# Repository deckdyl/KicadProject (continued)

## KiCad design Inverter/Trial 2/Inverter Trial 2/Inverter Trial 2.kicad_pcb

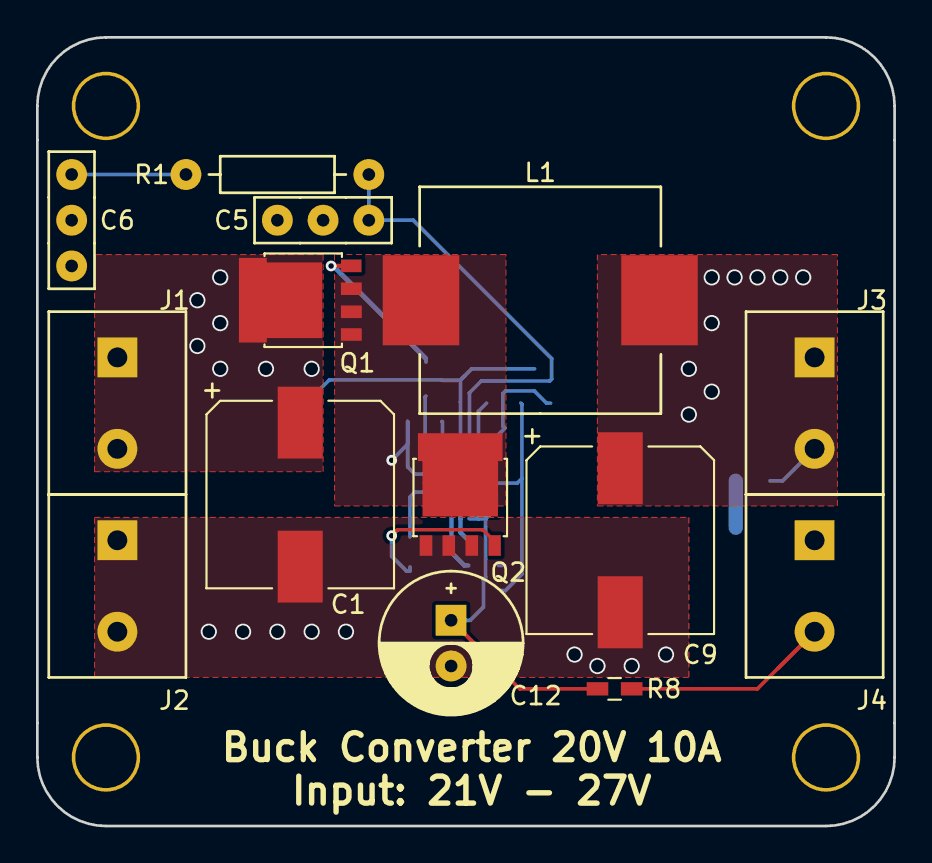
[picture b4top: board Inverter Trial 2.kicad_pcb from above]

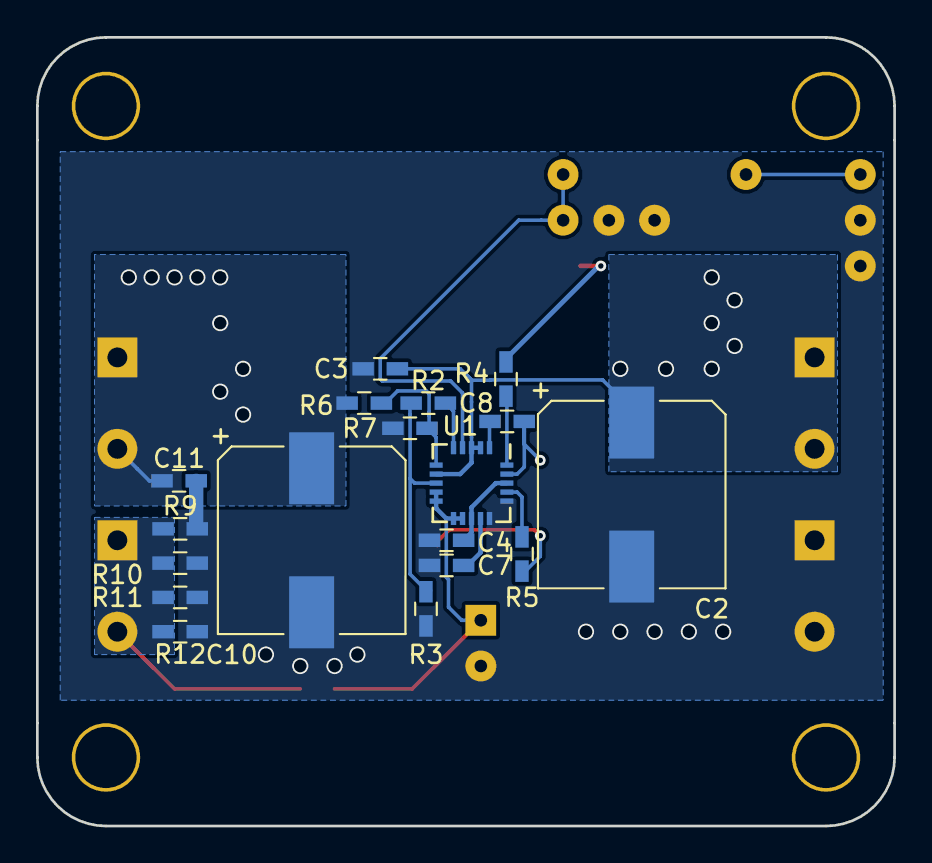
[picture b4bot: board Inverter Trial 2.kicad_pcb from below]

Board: 2 copper layers, 47.6 x 43.8 mm, 32 parts (18 on the bottom side), 18 nets.

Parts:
C1, C2, C9, C10: 330uF; CP_Elec_10x10.5
C3, C7, C8, C11: 100nF; C_0603_HandSoldering
C4: 1uF; C_0603_HandSoldering
C5: 220pF; Cap_UnPol_P3
C6: 2.2nF; Cap_UnPol_P3
C12: 10uF; Cap_Pol_Radial_D8_P2
J1: Battery+; Terminal_Block-5mm
J2: Battery-; Terminal_Block-5mm
J3: Vout+; Terminal_Block-5mm
J4: Vout-; Terminal_Block-5mm
L1: 2.2uH; Inductor_SMD_13X13
Q1, Q2: PSMN2R6-40YS; SOT-669_LFPAK
R1: 300kΩ; Resistor-0.25W
R2: 42.2kΩ; C_0603_HandSoldering
R3: 6.04kΩ; C_0603_HandSoldering
R4, R5, R8: 100Ω; C_0603_HandSoldering
R6: 18.7kΩ; C_0603_HandSoldering
R7: 1.2kΩ; C_0603_HandSoldering
R9, R10, R11, R12: 20mΩ; C_0603_HandSoldering
U1: TD8655; QFN-20-1EP_4x4mm_Pitch0.5mm

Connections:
/Vfb: R6.1, R7.2, U1.6
GND: C1.2, C2.2, C3.2, C4.2, C5.2, C6.2, C7.2, C9.2, C10.2, C11.2, C12.2, J2.1, J2.2, Q2.1, Q2.2, Q2.3, R3.1, R7.1, R9.1, R10.1, R11.1, R12.1, U1.15, U1.16
unnamed: C1.1, C2.1, C3.1, J1.1, J1.2, Q1.5, U1.2, U1.3, U1.7
unnamed: C4.1, U1.13, U1.18
unnamed: C5.1, R1.2, U1.4
unnamed: C6.1, R1.1
unnamed: C7.1, U1.14
unnamed: C8.1, U1.1
unnamed: C8.2, L1.1, Q1.1, Q1.2, Q1.3, Q2.5, U1.19
unnamed: C9.1, C10.1, C11.1, J3.1, J3.2, L1.2, R6.2
unnamed: C12.1, R8.2, U1.9, U1.10, U1.11, U1.12
unnamed: J4.1, J4.2, R8.1, R9.2, R10.2, R11.2, R12.2
unnamed: Q1.4, R4.1
unnamed: Q2.4, R5.1
unnamed: R2.1, R3.2, U1.8
unnamed: R2.2, U1.5
unnamed: R4.2, U1.20
unnamed: R5.2, U1.17

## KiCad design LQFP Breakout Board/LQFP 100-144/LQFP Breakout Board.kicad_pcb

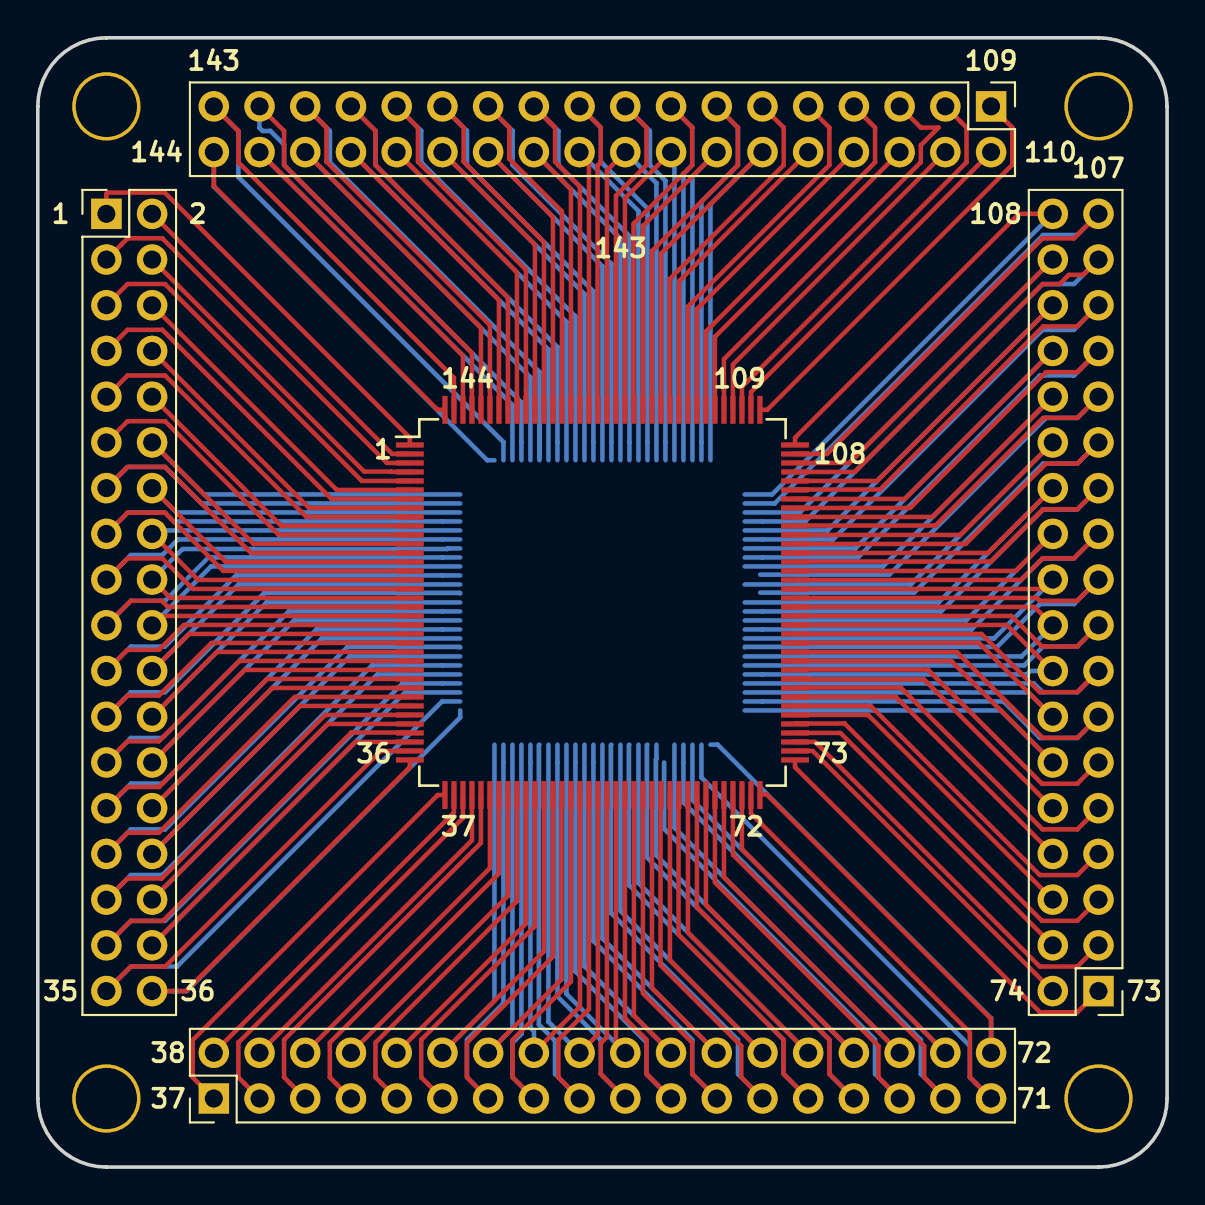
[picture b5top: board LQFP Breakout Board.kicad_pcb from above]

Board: 2 copper layers, 62.7 x 62.7 mm, 6 parts (1 on the bottom side), 144 nets.

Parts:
J1, J2, J3, J4: Conn_02x18_Odd_Even; Pin_Header_Straight_2x18_Pitch2.54mm
U1: STM32F446VET6; LQFP-100_14x14mm_Pitch0.5mm
U2: STM32F767ZITx; LQFP-144_20x20mm_Pitch0.5mm

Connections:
P01: J1.1, U2.1
P02: J1.2, U2.2
P03: J1.3, U2.3
P04: J1.4, U2.4
P05: J1.5, U2.5
P06: J1.6, U2.6
P07: J1.7, U2.7
P08: J1.8, U2.8
P09: J1.9, U2.9
P10: J1.10, U2.10
P11: J1.11, U2.11
P12: J1.12, U1.100, U2.12
P13: J1.13, U1.99, U2.13
P14: J1.14, U1.98, U2.14
P15: J1.15, U1.97, U2.15
P16: J1.16, U1.96, U2.16
P17: J1.17, U1.95, U2.17
P18: J1.18, U1.94, U2.18
P19: J1.19, U1.93, U2.19
P20: J1.20, U1.92, U2.20
P21: J1.21, U1.91, U2.21
P22: J1.22, U1.90, U2.22
P23: J1.23, U1.89, U2.23
P24: J1.24, U1.88, U2.24
P25: J1.25, U1.87, U2.25
P26: J1.26, U1.86, U2.26
P27: J1.27, U1.85, U2.27
P28: J1.28, U1.84, U2.28
P29: J1.29, U1.83, U2.29
P30: J1.30, U1.82, U2.30
P31: J1.31, U1.81, U2.31
P32: J1.32, U1.80, U2.32
P33: J1.33, U1.79, U2.33
P34: J1.34, U1.78, U2.34
P35: J1.35, U1.77, U2.35
P36: J1.36, U1.76, U2.36
P37: J2.1, U2.37
P38: J2.2, U2.38
P39: J2.3, U2.39
P40: J2.4, U2.40
P41: J2.5, U2.41
P42: J2.6, U2.42
P43: J2.7, U2.43
P44: J2.8, U2.44
P45: J2.9, U2.45
P46: J2.10, U2.46
P47: J2.11, U2.47
P48: J2.12, U1.75, U2.48
P49: J2.13, U1.74, U2.49
P50: J2.14, U1.73, U2.50
P51: J2.15, U1.72, U2.51
P52: J2.16, U1.71, U2.52
P53: J2.17, U1.70, U2.53
P54: J2.18, U1.69, U2.54
P55: J2.19, U1.68, U2.55
P56: J2.20, U1.67, U2.56
P57: J2.21, U1.66, U2.57
P58: J2.22, U1.65, U2.58
P59: J2.23, U1.64, U2.59
P60: J2.24, U1.63, U2.60
P61: J2.25, U1.62, U2.61
P62: J2.26, U1.61, U2.62
P63: J2.27, U1.60, U2.63
P64: J2.28, U1.59, U2.64
P65: J2.29, U1.58, U2.65
P66: J2.30, U1.57, U2.66
P67: J2.31, U1.56, U2.67
P68: J2.32, U1.55, U2.68
P69: J2.33, U1.54, U2.69
P70: J2.34, U1.53, U2.70
P71: J2.35, U1.52, U2.71
P72: J2.36, U1.51, U2.72
P73: J3.1, U2.73
P74: J3.2, U2.74
P75: J3.3, U2.75
P76: J3.4, U2.76
P77: J3.5, U2.77
P78: J3.6, U2.78
P79: J3.7, U2.79
P80: J3.8, U2.80
P81: J3.9, U2.81
P82: J3.10, U2.82
P83: J3.11, U2.83
P84: J3.12, U1.50, U2.84
P85: J3.13, U1.49, U2.85
P86: J3.14, U1.48, U2.86
P87: J3.15, U1.47, U2.87
P88: J3.16, U1.46, U2.88
P89: J3.17, U1.45, U2.89
P90: J3.18, U1.44, U2.90
P91: J3.19, U1.43, U2.91
P92: J3.20, U1.42, U2.92
P93: J3.21, U1.41, U2.93
P94: J3.22, U1.40, U2.94
P95: J3.23, U1.39, U2.95
P96: J3.24, U1.38, U2.96
P97: J3.25, U1.37, U2.97
P98: J3.26, U1.36, U2.98
P99: J3.27, U1.35, U2.99
P100: J3.28, U1.34, U2.100
P101: J3.29, U1.33, U2.101
P102: J3.30, U1.32, U2.102
P103: J3.31, U1.31, U2.103
P104: J3.32, U1.30, U2.104
P105: J3.33, U1.29, U2.105
P106: J3.34, U1.28, U2.106
P107: J3.35, U1.27, U2.107
P108: J3.36, U1.26, U2.108
P109: J4.1, U2.109
P110: J4.2, U2.110
P111: J4.3, U2.111
P112: J4.4, U2.112
P113: J4.5, U2.113
P114: J4.6, U2.114
P115: J4.7, U2.115
P116: J4.8, U2.116
P117: J4.9, U2.117
P118: J4.10, U2.118
P119: J4.11, U2.119
P120: J4.12, U1.25, U2.120
P121: J4.13, U1.24, U2.121
P122: J4.14, U1.23, U2.122
P123: J4.15, U1.22, U2.123
P124: J4.16, U1.21, U2.124
P125: J4.17, U1.20, U2.125
P126: J4.18, U1.19, U2.126
P127: J4.19, U1.18, U2.127
P128: J4.20, U1.17, U2.128
P129: J4.21, U1.16, U2.129
P130: J4.22, U1.15, U2.130
P131: J4.23, U1.14, U2.131
P132: J4.24, U1.13, U2.132
P133: J4.25, U1.12, U2.133
P134: J4.26, U1.11, U2.134
P135: J4.27, U1.10, U2.135
P136: J4.28, U1.9, U2.136
P137: J4.29, U1.8, U2.137
P138: J4.30, U1.7, U2.138
P139: J4.31, U1.6, U2.139
P140: J4.32, U1.5, U2.140
P141: J4.33, U1.4, U2.141
P142: J4.34, U1.3, U2.142
P143: J4.35, U1.2, U2.143
P144: J4.36, U1.1, U2.144

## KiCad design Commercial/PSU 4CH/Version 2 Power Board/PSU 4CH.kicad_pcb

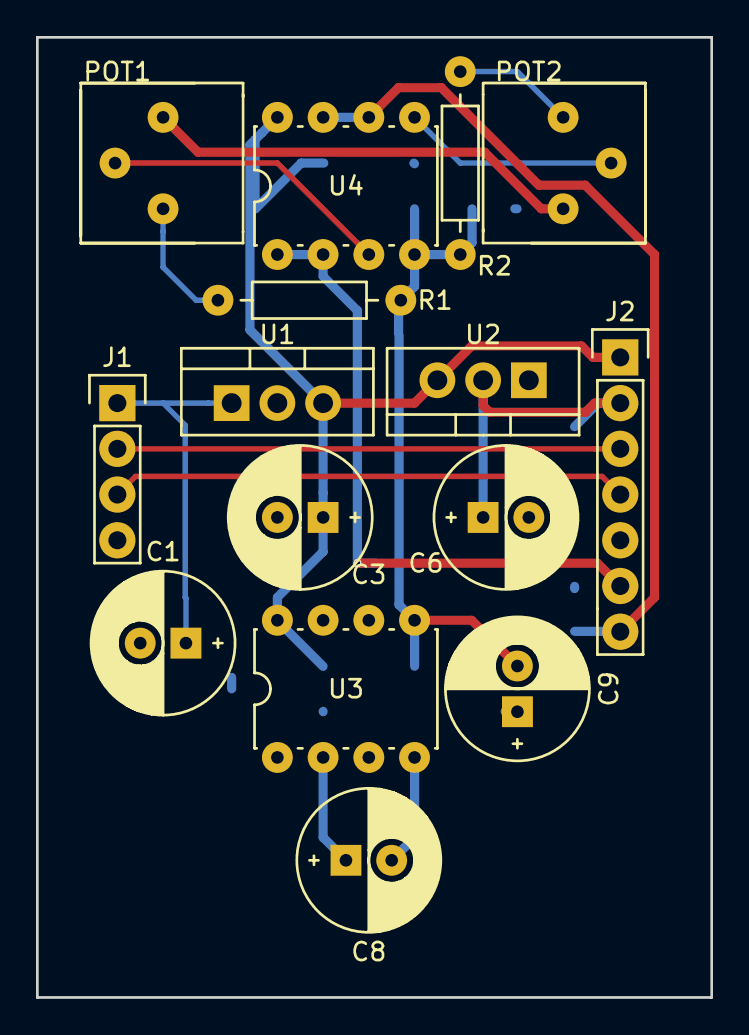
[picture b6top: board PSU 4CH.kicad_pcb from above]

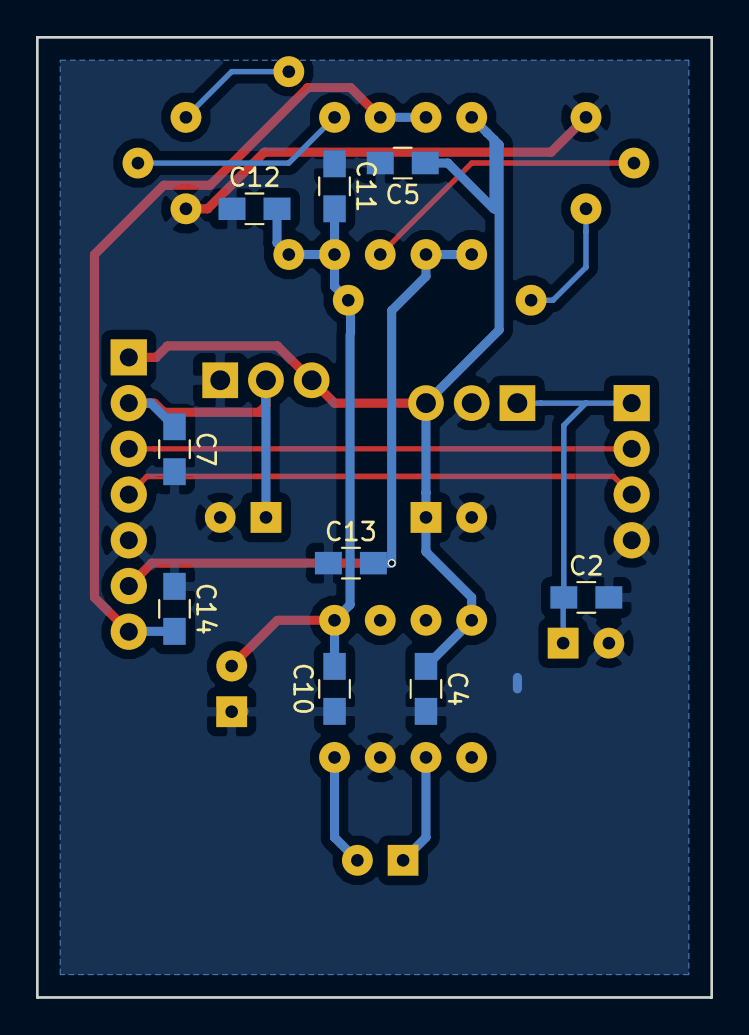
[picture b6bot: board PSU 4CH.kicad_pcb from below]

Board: 2 copper layers, 37.5 x 53.3 mm, 24 parts (9 on the bottom side), 15 nets.

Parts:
C1, C3, C6, C8, C9: 10uF; Cap_Pol_Radial_D8_P2
C2, C4, C5, C7, C10, C11, C12, C13, C14: 100nF; C_0805_HandSoldering
J1: I/O; Pin_Header_Straight_1x04
J2: PSU 4CH I/O; Pin_Header_Straight_1x07
POT1: 1kΩ; Potentiometer_Bourns_3386
POT2: 10K; Potentiometer_Bourns_3386
R1: 7K5; Resistor-0.25W
R2: 6K8; Resistor-0.25W
U1: L7805; TO-220_Neutral123_Vertical
U2: LD1117-3V3; TO-220_Neutral123_Vertical
U3: TC7662; IC_PDIP_8pin
U4: LM358; IC_PDIP_8pin

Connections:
+3V3: C6.1, C7.1, J2.2, U2.2
+5V: C3.1, C4.1, C5.1, J2.1, U1.3, U2.3, U3.8, U4.8
-0V5: C13.2, J2.6, U4.1, U4.2
-2V8: C14.2, J2.7, U4.6, U4.7
-5V: C9.2, C10.2, C11.2, C12.2, R1.1, R2.1, U3.5, U4.4
GND: C1.2, C2.2, C3.2, C4.2, C5.2, C6.2, C7.2, C9.1, C10.1, C11.1, C12.1, C13.1, C14.1, J1.4, J2.5, POT1.3, POT2.3, U1.2, U2.1, U3.3
unnamed: C8.1, U3.2
unnamed: C8.2, U3.4
unnamed: J1.2, J2.3
unnamed: J1.3, J2.4
unnamed: POT1.1, R1.2
unnamed: POT1.2, U4.3
unnamed: POT2.1, R2.2
unnamed: POT2.2, U4.5
Vin: C1.1, C2.1, J1.1, U1.1

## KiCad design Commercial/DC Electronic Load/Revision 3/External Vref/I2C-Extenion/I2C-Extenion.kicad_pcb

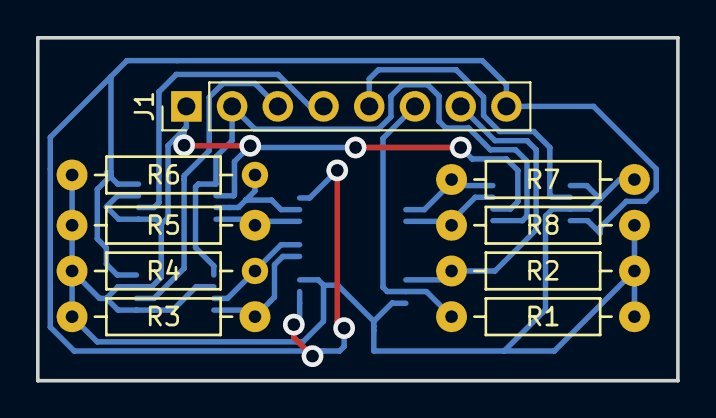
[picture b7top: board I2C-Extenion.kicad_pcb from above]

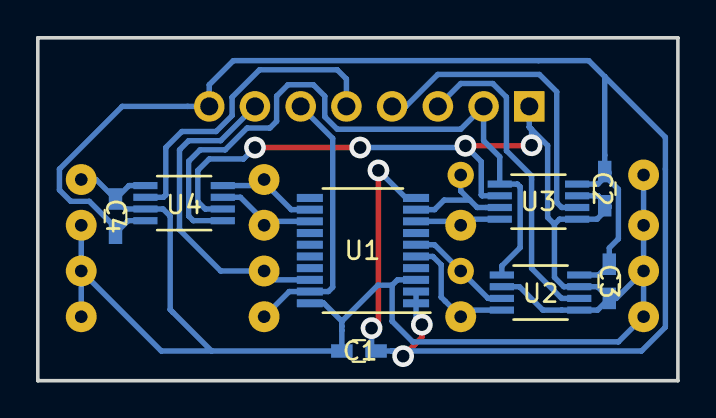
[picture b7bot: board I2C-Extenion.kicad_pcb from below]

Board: 2 copper layers, 35.6 x 19.1 mm, 17 parts (8 on the bottom side), 14 nets.

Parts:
C1, C2, C3, C4: 100nF; C_0603_HandSoldering
J1: Connector; Pin_Header_Straight_1x08_Pitch2.54mm
R1, R2, R3, R4, R5, R6, R7, R8: 10kΩ; Resistor-0.25W
U1: PCA9545; TSSOP-20_4.4x6.5mm_Pitch0.65mm
U2, U3, U4: MAX5215; uMAX

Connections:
1V-REF: J1.3, U2.6
2V5-REF: J1.4, U3.6
4V-REF: J1.5, U4.6
5V-REF: J1.2, U2.1, U3.1, U4.1
+3V3: C1.1, C2.1, C3.1, C4.1, J1.1, R1.1, R2.1, R3.1, R4.1, R5.1, R6.1, R7.1, R8.1, U1.3, U1.20, U2.2, U2.5, U2.7, U3.2, U3.5, U3.7, U4.2, U4.5, U4.7
GND: C1.2, C2.2, C3.2, C4.2, J1.8, U1.1, U1.2, U1.10, U2.8, U3.8, U4.8
I2C_SCL: J1.7, R2.2, U1.18
I2C_SDA: J1.6, R1.2, U1.19
unnamed: R3.2, U1.5, U2.4
unnamed: R4.2, U1.6, U2.3
unnamed: R5.2, U1.8, U3.4
unnamed: R6.2, U1.9, U3.3
unnamed: R7.2, U1.12, U4.4
unnamed: R8.2, U1.13, U4.3

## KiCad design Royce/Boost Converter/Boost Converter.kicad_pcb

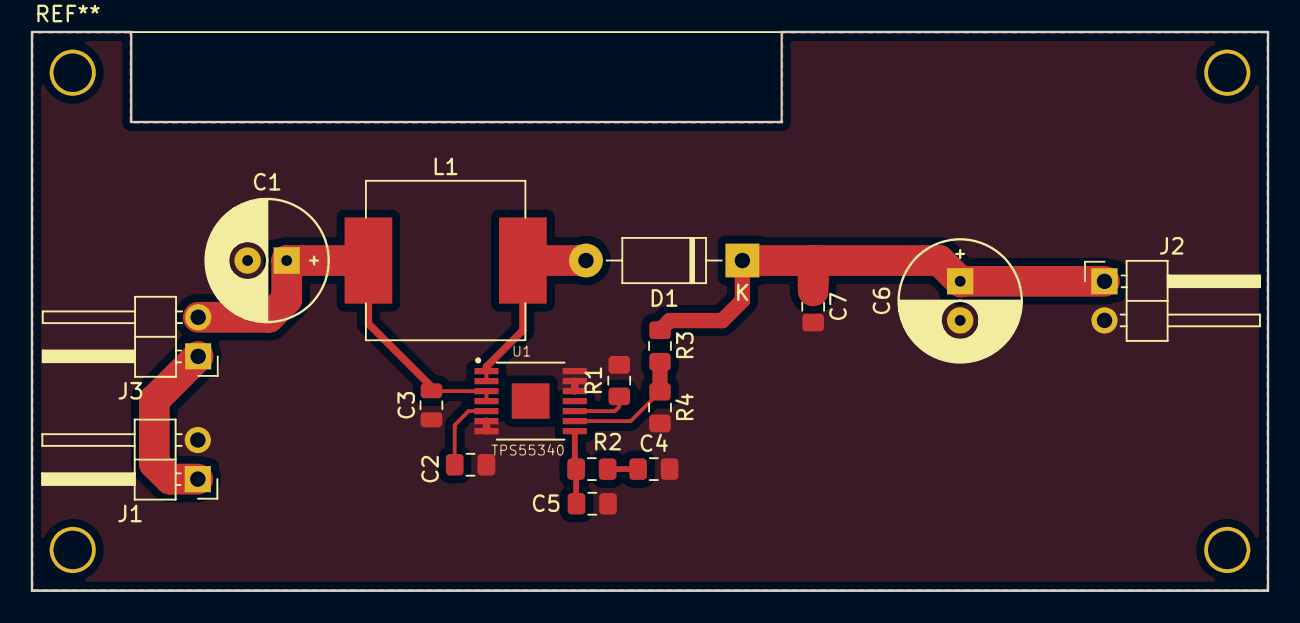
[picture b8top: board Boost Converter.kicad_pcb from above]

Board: 2 copper layers, 80.3 x 36.3 mm, 17 parts (0 on the bottom side), 10 nets.

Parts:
C1: 33u; Cap_Pol_Radial_D8_P2
C2: 22n; C_0805_2012Metric_Pad1.15x1.40mm_HandSolder
C3: 100n; C_0805_2012Metric
C4: 27n; C_0805_2012Metric_Pad1.15x1.40mm_HandSolder
C5: 820p; C_0805_2012Metric_Pad1.15x1.40mm_HandSolder
C6: 47u; Cap_Pol_Radial_D8_P2
C7: 1u; C_0805_2012Metric_Pad1.15x1.40mm_HandSolder
D1: 1N5818; D_DO-41_SOD81_P10.16mm_Horizontal
J1, J2: Conn_01x02_Male; PinHeader_1x02_P2.54mm_Horizontal
J3: Switch; PinHeader_1x02_P2.54mm_Horizontal
L1: 6.8uH; B82477R4684M100
R1: 38.3k; R_0805_2012Metric_Pad1.15x1.40mm_HandSolder
R2: 2.32k; R_0805_2012Metric_Pad1.15x1.40mm_HandSolder
R3: 88.2k; R_0805_2012Metric_Pad1.15x1.40mm_HandSolder
R4: 10k; R_0805_2012Metric_Pad1.15x1.40mm_HandSolder
U1: TPS55340; SOP65P640X120-15N

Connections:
GND: C1.2, C2.2, C3.2, C4.2, C5.2, C6.2, C7.2, J1.2, J2.2, R1.2, R4.2, U1.6, U1.7, U1.12, U1.13, U1.14
unnamed: C1.1, C3.1, J3.2, L1.1, U1.3, U1.4
unnamed: C2.1, U1.5
unnamed: C4.1, R2.2
unnamed: C5.1, R2.1, U1.8
unnamed: C6.1, C7.1, D1.1, J2.1, R3.1
unnamed: D1.2, L1.2, U1.1, U1.2
unnamed: J1.1, J3.1
unnamed: R1.1, U1.10
unnamed: R3.2, R4.1, U1.9

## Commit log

2018-08-12 Update from Local
    Update from Power i7 local data, first sync
2018-09-07 update 2018-09-07 2019H
2018-09-07 Added schematic symbol PCA9545
2018-09-07 DC-electronic Load I2C extension Schematic Complete
    Vref for the DC Electronic Load Revision 3 had some issue bacause the MAX5215 were interfering with each other so I decided to use an I2C multiplexer to split them, hopefully it works...
2018-09-08 DC Electronic Load I2C Extension PCB Complete
2018-10-08 New Project
2018-10-19 PSU 4CH V1 Schematic Complete
2019-01-03 PSU 4CH design complete
2019-01-03 PSU 4CH Power Board Created
2019-01-05 PSU 4CH Power Board Gerber Generated
2019-01-05 PSU 4CH V2 Power Board Geber Re-generated with protel extentions
2019-01-06 LQFP Breakout Board
    LAQF Breakout board for LQFP 100 and LQFP 144 Created
2019-01-21 Inverter Trial 2 Buck converter schematic design complete
2019-01-24 Inverter Buck Converter Section PCB completed
2019-04-20 Add MCP3425 to Schematic Library
2019-06-14 Added MAX4525 to CustomLibrary
2019-12-05 Added ADP3605
2019-12-05 Update 05/12/19
2019-12-05 TL431 schematic diagram modified
